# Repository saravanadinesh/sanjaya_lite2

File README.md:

# Sanjaya Lite2
This is the second, improved version of the Sanjaya lite design. Following are the major changes/improvements:
1. The power supply circuitry: Overvoltage protection has been removed, transient protection added, and a large tank capacitor has been added
2. Footprints of slap-on boards adjusted to be more accurate
3. TXB0104 added between ESP32 and SIM800 
4. Transient protection added for RS485

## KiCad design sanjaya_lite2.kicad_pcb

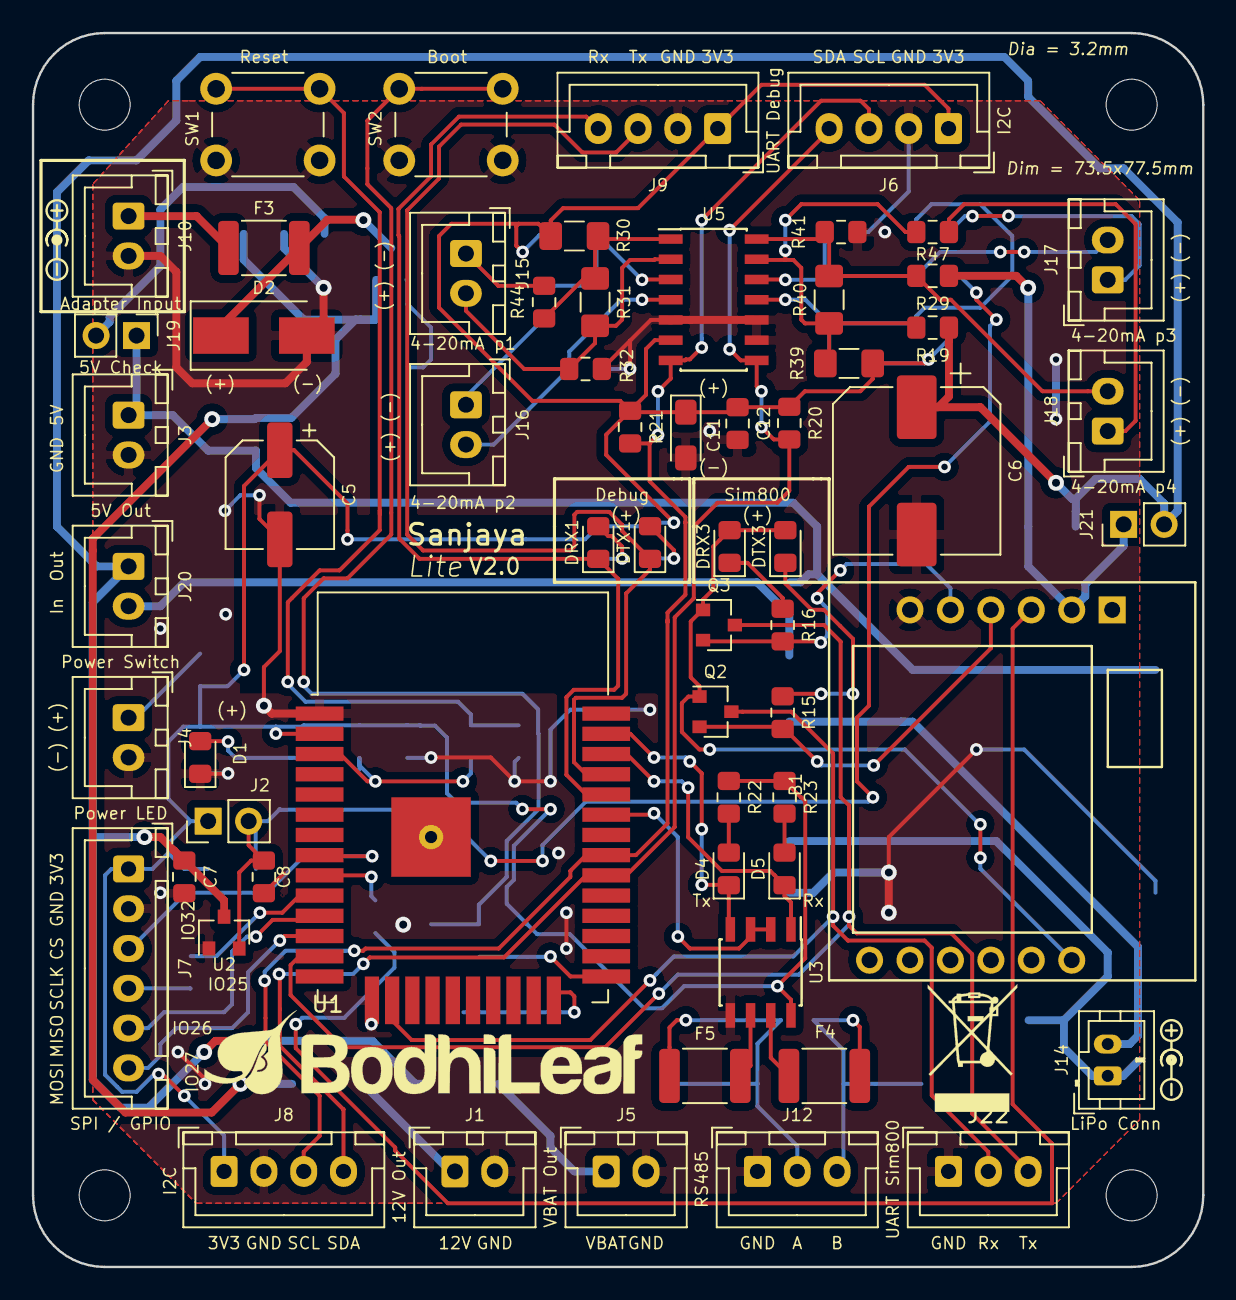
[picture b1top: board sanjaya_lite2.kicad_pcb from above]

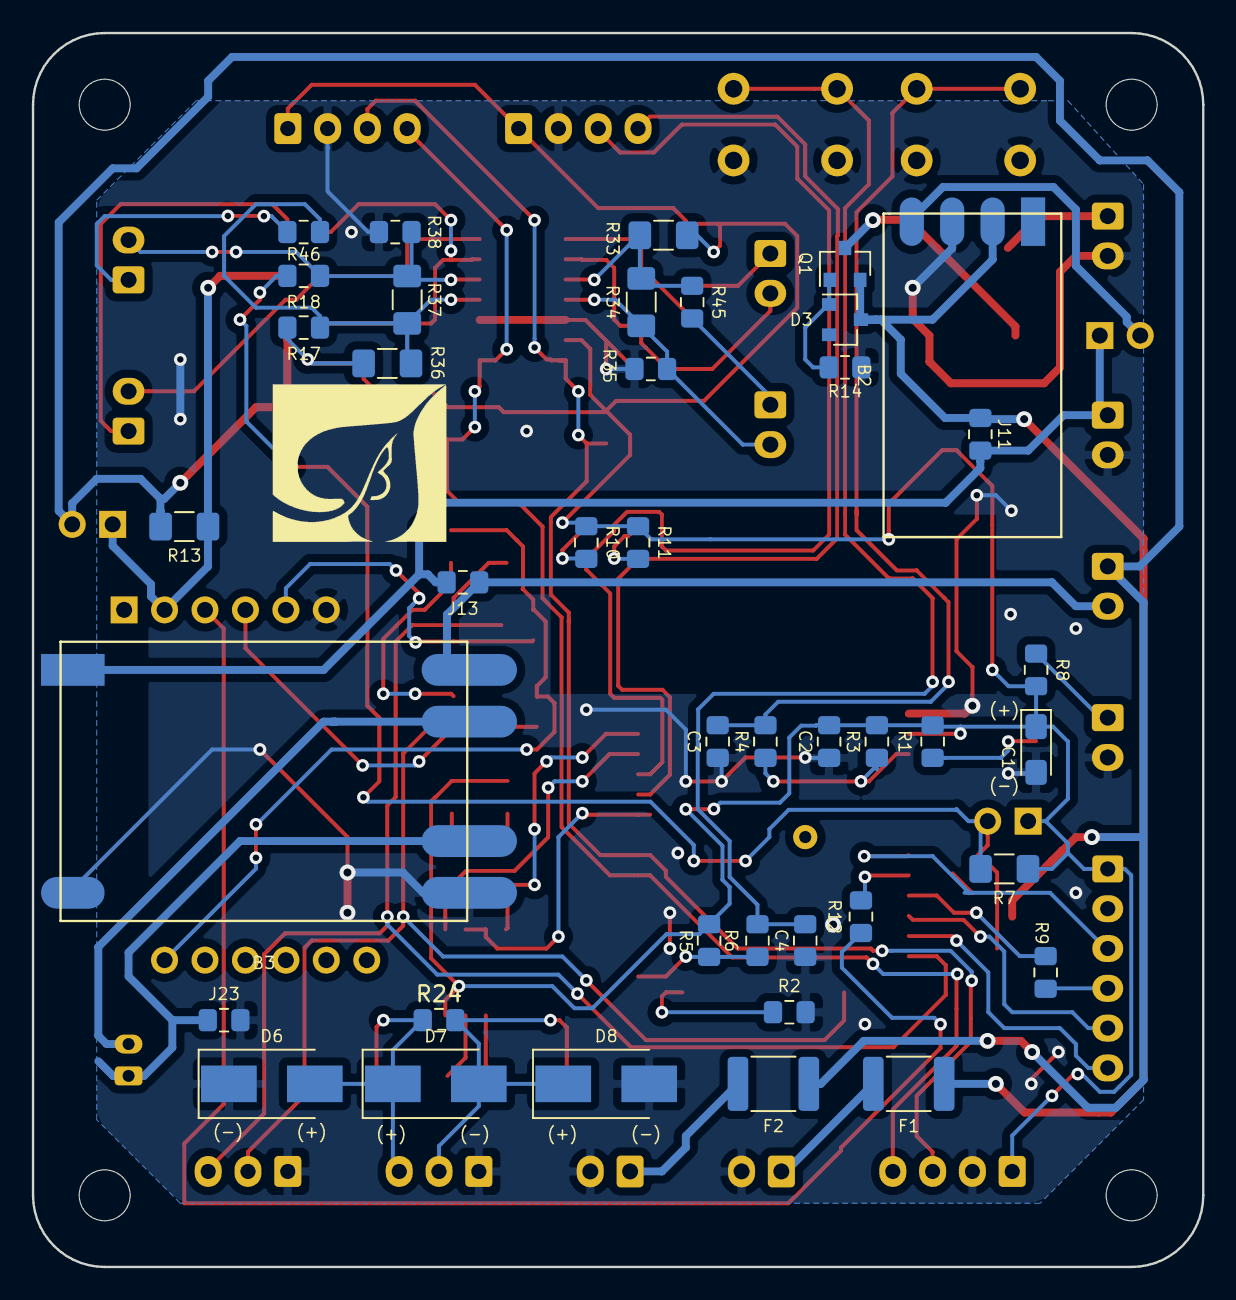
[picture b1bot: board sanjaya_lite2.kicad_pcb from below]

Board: 2 copper layers, 73.5 x 77.5 mm, 103 parts (41 on the bottom side), 64 nets.

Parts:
B1: SIM800L; Sim800L_Module
B2: MP2315_DCDC_Board; MCP2315_Module
B3: TPS4056_Board; TP4056_Module
C1, C11: 10uF; CP_EIA-3216-10_Kemet-I_Pad1.58x1.35mm_HandSolder
C2, C12: 0.1uF; C_0805_2012Metric_Pad1.15x1.40mm_HandSolder
C3, C4: 1nF; C_0805_2012Metric_Pad1.15x1.40mm_HandSolder
C5: 100uF; CP_Elec_6.3x5.4
C6: 1000uF; CP_Elec_10x10
C7, C8: 1uF; C_0805_2012Metric_Pad1.15x1.40mm_HandSolder
D1: Green; LED_0805_2012Metric_Pad1.15x1.40mm_HandSolder
D2, D6, D7, D8: TVS_SMBJ30CA; D_SMB_Handsoldering
D3: Z10V; D_SOT-23_ANK
D4: LED_G; LED_0805_2012Metric_Pad1.15x1.40mm_HandSolder
D5: LED_R; LED_0805_2012Metric_Pad1.15x1.40mm_HandSolder
DRX1, DRX3: Red; LED_0805_2012Metric_Pad1.15x1.40mm_HandSolder
DTX1, DTX3: Red; LED_0805_2012Metric_Pad1.15x1.40mm_HandSolder
F1, F2, F4, F5: 500mA; Fuse_1812_4532Metric_Pad1.30x3.40mm_HandSolder
F3: PPTC_1A; Fuse_1812_4532Metric_Pad1.30x3.40mm_HandSolder
J1: 12V_Out; JST_XH_B02B-XH-A_1x02_P2.50mm_Vertical
J2: J_SW_Esp; PinHeader_1x02_P2.54mm_Vertical
J3: 5V_Out; JST_XH_B02B-XH-A_1x02_P2.50mm_Vertical
J4: J_LED; JST_XH_B02B-XH-A_1x02_P2.50mm_Vertical
J5: VBat_Out; JST_XH_B02B-XH-A_1x02_P2.50mm_Vertical
J6, J8: Conn_I2C; JST_XH_B04B-XH-A_1x04_P2.50mm_Vertical
J7: Conn_SPI; JST_XH_B06B-XH-A_1x06_P2.50mm_Vertical
J9: J_UART_DBG; JST_XH_B04B-XH-A_1x04_P2.50mm_Vertical
J10: Adap_In; JST_XH_B02B-XH-A_1x02_P2.50mm_Vertical
J11: DCDC_Bypass; R_0805_2012Metric_Pad1.15x1.40mm_HandSolder
J12: Conn_RS485; JST_XH_B03B-XH-A_1x03_P2.50mm_Vertical
J13: Bat_Bypass+; R_0805_2012Metric_Pad1.15x1.40mm_HandSolder
J14: J_Bat; JST_PH_B2B-PH-K_1x02_P2.00mm_Vertical
J15: Conn_420_1; JST_XH_B02B-XH-A_1x02_P2.50mm_Vertical
J16: Conn_420_2; JST_XH_B02B-XH-A_1x02_P2.50mm_Vertical
J17: Conn_420_3; JST_XH_B02B-XH-A_1x02_P2.50mm_Vertical
J18: Conn_420_4; JST_XH_B02B-XH-A_1x02_P2.50mm_Vertical
J19: Volt_check_5V; PinHeader_1x02_P2.54mm_Vertical
J20: Pwr_SW; JST_XH_B02B-XH-A_1x02_P2.50mm_Vertical
J21: J_SW_Sim800; PinHeader_1x02_P2.54mm_Vertical
J22: UART_Sim800; JST_XH_B03B-XH-A_1x03_P2.50mm_Vertical
J23: Bat_Prot_Bypass; R_0805_2012Metric_Pad1.15x1.40mm_HandSolder
Q1: PMOS_SI2369DS; SOT-23
Q2, Q3: BSS138; SOT-23
R1, R8, R10, R11, R15, R16, R22: 330; R_0805_2012Metric_Pad1.15x1.40mm_HandSolder
R2, R20, R21, R23: 1K; R_0805_2012Metric_Pad1.15x1.40mm_HandSolder
R3, R5, R14: 10K; R_0805_2012Metric_Pad1.15x1.40mm_HandSolder
R4, R6: 470; R_0805_2012Metric_Pad1.15x1.40mm_HandSolder
R7, R13: 1m; R_1206_3216Metric_Pad1.42x1.75mm_HandSolder
R9: 330orZero; R_0805_2012Metric_Pad1.15x1.40mm_HandSolder
R12, R17, R18, R19, R29, R32, R35, R38, R41: 0; R_0805_2012Metric_Pad1.15x1.40mm_HandSolder
R24: 120; R_0805_2012Metric_Pad1.15x1.40mm_HandSolder
R30, R33, R36, R39: 1K_1%; R_1206_3216Metric_Pad1.42x1.75mm_HandSolder
R31, R34, R37, R40: 100_1%; R_1206_3216Metric_Pad1.42x1.75mm_HandSolder
R44, R45, R46, R47: 100; R_0805_2012Metric_Pad1.15x1.40mm_HandSolder
SW1: SW_Reset; SW_PUSH_6mm_H4.3mm
SW2: SW_Boot; SW_PUSH_6mm_H4.3mm
U1: ESP32-WROOM-32; ESP32-WROOM-32_Handsolder
U2: MCP1700-3302E_SOT23; SOT-23
U3: SN65HVD75DR; SOIC-8_3.9x4.9mm_P1.27mm
U5: MCP3428; SOIC-14_3.9x8.7mm_P1.27mm

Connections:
/5V_Out: B3.1, J3.1, J11.1, J13.2, J19.1
/12V_Out: B2.2, D3.1, F1.1, J11.2, Q1.2
/BOOT_IO0: R5.2, R6.1, U1.25
/BOOT_IO2: R2.1, U1.24
/CS: J7.3, U1.8
/EN: R3.2, R4.1, U1.3
/Esp_I_Sense+: C1.1, C2.1, C5.1, C11.1, C12.1, J2.1, J6.1, J7.1, J8.1, J9.1, R1.1, R3.1, R5.1, R7.1, R8.2, R10.1, R11.1, R17.2, R20.1, R21.1, R22.1, R23.1, R30.1, R33.1, R36.1, R39.1, U1.2, U3.8, U5.6
/Esp_I_Sense-: C8.1, J2.2, R7.2, R18.2, U2.2
/GND_Supply: B1.6, B2.3, B3.2, B3.3, C1.2, C2.2, C3.2, C4.2, C5.2, C6.2, C7.2, C8.2, C11.2, C12.2, D1.1, D2.2, D6.1, D8.2, J1.2, J3.2, J4.2, J5.2, J6.2, J7.2, J8.2, J9.2, J10.2, J12.1, J22.1, J23.2, R2.2, R14.2, R32.2, R35.2, R38.2, R41.2, SW1.2, SW2.2, U1.1, U1.15, U1.38, U2.1, U3.5, U5.5, U5.9, U5.10
/MISO_RLY1: J7.5, U1.11
/MOSI_RLY2: J7.6, U1.12
/SCL: J6.3, J8.3, R21.2, U1.31, U5.7
/SCLK: R9.1, U1.10
/SDA: J6.4, J8.4, R20.2, U1.30, U5.8
/Sim800_I_Sense+: C6.1, C7.1, F2.1, J20.1, J21.2, R13.2, R19.2, U2.3
/Sim800_I_Sense-: B1.2, J21.1, R13.1, R29.2
/Sim800_RST: B1.3, R12.1
/rs485/A: D7.2, D8.1, F5.1, J12.2, R24.2
/rs485/B: D6.2, D7.1, F4.1, J12.3, R24.1
/rs485/DE: U1.33, U3.2, U3.3
/rs485/DI: D4.1, U1.37, U3.4
/rs485/RO: D5.1, U1.36, U3.1
unnamed: B1.4, Q2.2, R15.2
unnamed: B1.5, Q3.2, R16.2
unnamed: B1.12, DRX3.2, DTX3.2, Q2.1, Q3.1
unnamed: B2.4, J19.2
unnamed: B3.4, J14.1, J23.1
unnamed: B3.5, J14.2
unnamed: B3.6, J13.1, J20.2
unnamed: C3.1, R4.2, SW1.1
unnamed: C4.1, R6.2, SW2.1
unnamed: D1.2, R1.2
unnamed: D2.1, F3.1, Q1.3
unnamed: D3.2, Q1.1, R14.1
unnamed: D4.2, R22.2
unnamed: D5.2, R23.2
unnamed: DRX1.1, J9.4, U1.34
unnamed: DRX1.2, R11.2
unnamed: DRX3.1, R16.1
unnamed: DTX1.1, J9.3, U1.35
unnamed: DTX1.2, R10.2
unnamed: DTX3.1, R15.1
unnamed: F1.2, J1.1
unnamed: F2.2, J5.1
unnamed: F3.2, J10.1
unnamed: F4.2, U3.7
unnamed: F5.2, U3.6
unnamed: J4.1, R8.1
unnamed: J7.4, R9.2
unnamed: J15.1, R44.2
unnamed: J15.2, R31.2, R32.1, U5.2
unnamed: J16.1, R45.2
unnamed: J16.2, R34.2, R35.1, U5.4
unnamed: J17.1, R46.2
unnamed: J17.2, R18.1, R37.2, R38.1, U5.12
unnamed: J18.1, R47.2
unnamed: J18.2, R29.1, R40.2, R41.1, U5.14
unnamed: J22.2, Q2.3, U1.16
unnamed: J22.3, Q3.3, U1.13
unnamed: R12.2, U1.9
unnamed: R17.1, R36.2, R37.1, R46.1, U5.11
unnamed: R19.1, R39.2, R40.1, R47.1, U5.13
unnamed: R30.2, R31.1, R44.1, U5.1
unnamed: R33.2, R34.1, R45.1, U5.3

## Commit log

2019-04-12 Sch files copied from sanjaya_lite project. No mods added yet.
2019-04-13 1. Removed overvoltage protection from power supply, added transient protection, changed LDO 2. Added TXB0104 between ESP32 and Sim800 (partially done)
2019-04-14 1. Removed TXB0104 and added a simply NMOS based level shifter circuit 2. Added TVS protection for RS485 outputs 3. Changed ADC supply voltage to 3V3. Removed VBAT sensing and instead added current s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
2019-04-15 Schematics draft 1 complete
2019-04-16 Footprint association done
2019-04-16 Minor footprint changes added. Schematic is now layout ready (pending review)
2019-04-16 Layout started. Incomplete
2019-04-17 Basic board layout with connectors and large components done
2019-04-17 Made some changes to the layout. It is still incomplete
2019-04-18 Most of the layout done. Some power supply related components are the only ones remaining
2019-04-18 First layout draft
2019-04-21 Created a 1A net class
2019-04-21 Some routing done. Minor changes to schematics.
2019-04-21 Routing for ESP, Sim800, RS485 done. ADC and terminal routing not yet done.
2019-04-22 Routing other than ground signal completed
2019-04-22 Ground pour on F.Cu and B.Cu added. DRC still not passing. Checking in to save work
2019-04-22 No unconnected tracks. DRC not passing due to one minor issue: ESP pad 39 and solder pad behind it not connected. This is because pad 39 doesn't show up in the schematic and the solder pad behind it 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
2019-04-22 DRC passing after ESP footprint was edited for the thermal pad. Edge cut layer added
2019-04-23 1. Corrected a schematics error where power switch was not cutting power off to VBAT. Made corresponding changes to pcb layout and routing 2. LDO physical location was causing problems with new routi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
2019-04-23 Text added. J11 and J13 were found to be underneath dc-dc board footprint. Need to repair it
2019-04-23 Bat_Bypass jumper resistor moved out of DC-DC board's footprint. DC-DC bypass jumper resistor left where it was as it will be soldered only when the DC-DC board isn't present
2019-04-24 Battery JST pin connections swapped. Copper pour restricted near Sim800 antenna area
2019-05-03 Reversed the battery polarity silk screen symbol as it was wrong. Added polarity indication on F.Silk for D1
2019-05-04 Adding pdf of schematic
2019-05-24 Kicad forced to refill zones. But actually no change from previous commit except new gerber files have been generated
